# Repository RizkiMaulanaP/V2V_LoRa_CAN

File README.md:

# V2V LoRa CAN — Vehicle-to-Vehicle Collision Warning System

A research prototype for **vehicle-to-vehicle (V2V) safety messaging over LoRa**.
Each vehicle fuses GPS + IMU + OBD-II data, broadcasts its state to nearby
vehicles over a long-range LoRa link, and warns the driver (visual dashboard +
audible buzzer) of collision threats computed from the relative motion of
neighbours.

```
 ┌───────────── Vehicle A ─────────────┐         ┌──── Vehicle B ────┐
 │  GPS ┐                                │         │                   │
 │  IMU ┼─► ESP32 MCU ──USB──► Pi host   │  LoRa   │   ESP32 MCU ...   │
 │  OBD ┘   (firmware)  CDC   (UKF +     │◄═══════►│                   │
 │            │                warnings) │ 921 MHz │                   │
 │         GP4 buzzer ◄──CMD_BUZZER──┘   │         └───────────────────┘
 │            │                  │ TCP JSON :8765
 │         3 status LEDs         ▼
 └────────────────────────  Flutter dashboard (phone / desktop)
```

- **Firmware** (ESP32 / SX1262) — sensor acquisition, LoRa TX/RX, buzzer + LEDs.
- **Host** (Python on a Raspberry Pi / laptop) — UKF sensor fusion, neighbour
  tracking, the collision-warning engine, and the JSON bridge to the app.
- **App** (Flutter) — the driver dashboard (gauges + differentiated warnings).
- **Simulator** — replays recorded drives into the app, no hardware needed.

See [`MEMORY.md`](MEMORY.md) for a condensed design reference.

---

## 1. Hardware (per vehicle)

| Block | Part | Interface |
|-------|------|-----------|
| MCU + radio | Heltec ESP32 + **SX1262** LoRa (Wireless-Tracker class) | — |
| GNSS | on-board GNSS (UC6580-class) | UART `Serial1` 115200, RX=GP33 TX=GP34, power enable GP3 |
| IMU | **BMI160** (accel ±8 g, gyro ±500 °/s) | SPI, CS=GP7 |
| CAN / OBD-II | **MCP2515** (8 MHz xtal) @ 500 kbit/s | SPI, CS=GP15, INT=GP16 |
| Display | ST7735 TFT (on-board) | — |
| Annunciator | active buzzer | GP4 |
| Status LEDs | CAN / LoRa / GPS activity | GP17 / GP6 / GP5 |
| Host link | USB CDC serial @ 921600 | — |

**Shared SPI bus** (MCP2515 + BMI160): SCK=GP9, MISO=GP11, MOSI=GP10.
PCB design files in [`pcb-design/`](pcb-design/).

---

## 2. LoRa radio

| Parameter | Value |
|-----------|-------|
| Frequency | 921 MHz (AS923) |
| TX power | 20 dBm |
| Bandwidth | 125 kHz |
| Spreading factor | **SF9** |
| Coding rate | 4/8 |
| Modem | LoRa, explicit header, CRC on |
| Airtime | ≈ 250 ms / frame (11-byte payload) |

### Transmit triggering — ETSI CAM-style
Instead of a fixed interval, a node broadcasts when its state has *changed
meaningfully*, so fast/turning vehicles update more often and parked ones go
quiet. Evaluated every 100 ms; transmit when **any** of:

- position moved **> 4 m**, or
- heading changed **> 4°**, or
- speed changed **≥ 2 km/h**,

bounded to **[500 ms, 2 s]** (the upper bound is a heartbeat). Hard-brake events
(EEBL) and host-driven alerts are sent immediately.

### Compact over-air payload — 11 bytes
To keep airtime low, the broadcast is a packed 11-byte message (vs a naïve
19-byte struct), little-endian per field:

| bytes | field | encoding | resolution |
|------|-------|----------|-----------|
| 0 | node_id (6b) \| alert (2b) | `(id<<2)\|alert` | 0..63 / 0..3 |
| 1 | heading | `v·360/256` | 1.41° |
| 2 | speed | km/h | 1 km/h |
| 3–5 | latitude | 24-bit, −90..+90 | ~1.2 m |
| 6–8 | longitude | 24-bit, −180..+180 | ~2.4 m |
| 9–10 | tx_ts | `millis() & 0xFFFF` | 1 ms (wraps 65 s) |

`alert`: `0` normal, `1` traffic-jam, `2` hard-brake. Codec + rationale in
[`examples/CompactPayload/`](examples/CompactPayload/).

---

## 3. Firmware (`V2V_LoRa_CAN.ino`)

`FW_VERSION 3`. Single-file Arduino sketch (Heltec ESP32 core).
> The `V2V_LoRa_TWAI/` folder is an alternate build using the ESP32 built-in
> TWAI controller instead of the MCP2515 — **not maintained / not in use**.

Responsibilities:
- **Sensor acquisition**: BMI160 @ 100 Hz, GNSS (TinyGPS++), OBD-II PID polling
  (speed / RPM / coolant) over CAN.
- **Host serial protocol** (USB CDC): length-typed frames
  `[0xAA | type | ts | payload | XOR-cksum | 0x55]`:

  | frame | id | bytes | contents |
  |-------|----|-------|----------|
  | IMU | 0x01 | 32 | ax/ay/az, gx/gy/gz |
  | GPS | 0x02 | 34 | lat/lon, speed, hdop, sats, fix |
  | OBD | 0x03 | 9 | speed |
  | OBD_EXT | 0x06 | 12 | RPM, coolant |
  | HELLO | 0x05 | 10 | node_id, fw_version |
  | LORA_RX | 0x04 | 30 | decoded neighbour + RSSI/SNR |

  Host→MCU commands `[0xBB | cmd | … | cksum | 0x55]`: `CMD_HELLO`,
  `CMD_UPDATE_STATE` (push fused pose back so broadcasts carry filtered data),
  `CMD_BROADCAST` (immediate alert), `CMD_BUZZER` (drive GP4; pattern in the
  alert byte).
- **LoRa**: pack/broadcast own state (compact), unpack neighbours in `OnRxDone`
  and forward to the host via `LORA_RX`.
- **EEBL**: `detectHardBrake()` flags own rapid deceleration (OBD speed drop) and
  broadcasts `ALERT_BRAKE` for ~2 s.
- **Buzzer** (GP4, full-volume, non-blocking pattern player): `1` warning = two
  quick beeps, `2` danger = that burst repeated ~2.5 s, `3` GPS = double-chirp.
- **Activity LEDs**: single non-blocking blink per CAN/LoRa/GPS event.

A standalone PWM buzzer-volume bench sketch lives in
[`examples/BuzzerPWM/`](examples/BuzzerPWM/) (production uses full volume).

---

## 4. Host (`python-app/`)

| File | Role |
|------|------|
| `main_ukf.py` | live host: reads MCU serial, runs fusion, streams JSON, drives buzzer |
| `v2v_fusion.py` | ego **UKF** (E,N,v,ψ) + per-neighbour **CTRV** Kalman tracks |
| `v2v_warnings.py` | shared collision-warning engine |
| `v2v_json.py` | JSON contract + threaded TCP broadcast server |
| `simulate_v2v.py` | CSV-replay host (no hardware) |
| `plot_path.py` | offline trajectory plot (ego + neighbours) |

### Warning engine
`assess(ego, neighbors, gps) → (warning, buzzer)`:

- **Closing speed & TTC** from relative velocity.
- **Speed-scaled thresholds** (TTC bands + headway distance, not fixed radii).
- **Path / approach filtering** (only converging, in-corridor neighbours warn;
  classifies forward / cross / rear).
- **EEBL** for a same-heading lead vehicle broadcasting a brake flag.
- **GPS-lost / low-accuracy** ego warning.
- Per-node buzzer cooldown (warning re-beeps ≤ once / 5 s; danger re-arms ~2.5 s).

### JSON contract (host → app, newline-delimited, TCP :8765)
```json
{
  "ts": 123456,
  "ego": {"lat","lon","x","y","speed_kmh","heading_deg",
          "engine_rpm","engine_temp_c","fuel_level_pct",
          "fix_valid","hdop","satellites"},
  "neighbors": [{"id","lat","lon","x","y","speed_kmh","heading_deg",
                 "emergency_status"}],
  "warning": {"level","type","direction","distance_m","ttc_s",
              "closing_kmh","neighbor_id"}   // or null
}
```
Full spec: [`Flutter-App/v2v/docs/DATA_CONTRACT.md`](Flutter-App/v2v/docs/DATA_CONTRACT.md).

---

## 5. App (`Flutter-App/v2v/`)

Driver dashboard: RPM + speed gauges, engine temp/fuel, and a central
**warning card**. Data sources are swappable in `home_screen.dart`:
`TcpDataSource` (live host / simulator), `MockDataSource` (offline CSV),
`SerialDataSource`, `JsonlFileDataSource`.

Warnings are **host-computed** and merely rendered, with differentiated types:
forward-collision, emergency-brake, cross-traffic, approaching-rear,
emergency-broadcast, GPS-lost — each with its own icon/colour, plus distance /
TTC / closing speed and a GPS-health chip.

---

## 6. Build & run

### Firmware
Arduino IDE / arduino-cli with the **Heltec ESP32** board package. Set a unique
`NODE_ID` per vehicle, flash both nodes (SF and air format must match → same
firmware version on every node), open serial @ 921600.

### Host
```bash
cd python-app
pip install pyserial numpy scipy matplotlib filterpy pandas
python main_ukf.py --json-tcp 8765           # auto-detect MCU; serve app on :8765
# pin the serial port if needed:
python main_ukf.py --port /dev/ttyACM0 --json-tcp 8765
```

### App
```bash
cd Flutter-App/v2v
flutter pub get
flutter run -d linux        # dashboard connects to localhost:8765
```
For a phone/tablet, set `TcpDataSource(host: '<PC-LAN-IP>')` in
`lib/presentation/screens/home_screen.dart` (server binds `0.0.0.0`).

### Simulator (no hardware)
```bash
cd python-app
python simulate_v2v.py --loop                # replay newest recording → :8765
python simulate_v2v.py --inject-brake 60     # demo an EEBL event at t=60 s
python simulate_v2v.py --serial /dev/ttyACM0 # also drive a bench buzzer
```

---

## 7. Repository layout
```
V2V_LoRa_CAN.ino        firmware (MCP2515 CAN variant — in use)
V2V_LoRa_TWAI/          firmware (ESP32 TWAI variant — unused)
python-app/             host, fusion, warning engine, simulator, tools
Flutter-App/v2v/        driver dashboard
examples/CompactPayload/ over-air payload codec + spec
examples/BuzzerPWM/     buzzer PWM volume bench sketch
pcb-design/             hardware design files
BMI160-Arduino/         IMU library
MEMORY.md               condensed design reference
```

---

## 8. Status & limitations
- Two-node tested; firmware is single-file and board-specific (Heltec).
- No listen-before-talk (CAD was evaluated and removed) — short CAM intervals
  raise collision exposure slightly.
- LoRa duty cycle exceeds the 1 % AS923 regulatory limit at short intervals;
  this is a **research prototype**, tune `CAM_T_MIN_MS` / SF for compliant use.
- `tx_ts` wraps every ~65 s (one-way latency only).
- Research/educational project — not a certified safety system.

## License
See [`LICENSE`](LICENSE).

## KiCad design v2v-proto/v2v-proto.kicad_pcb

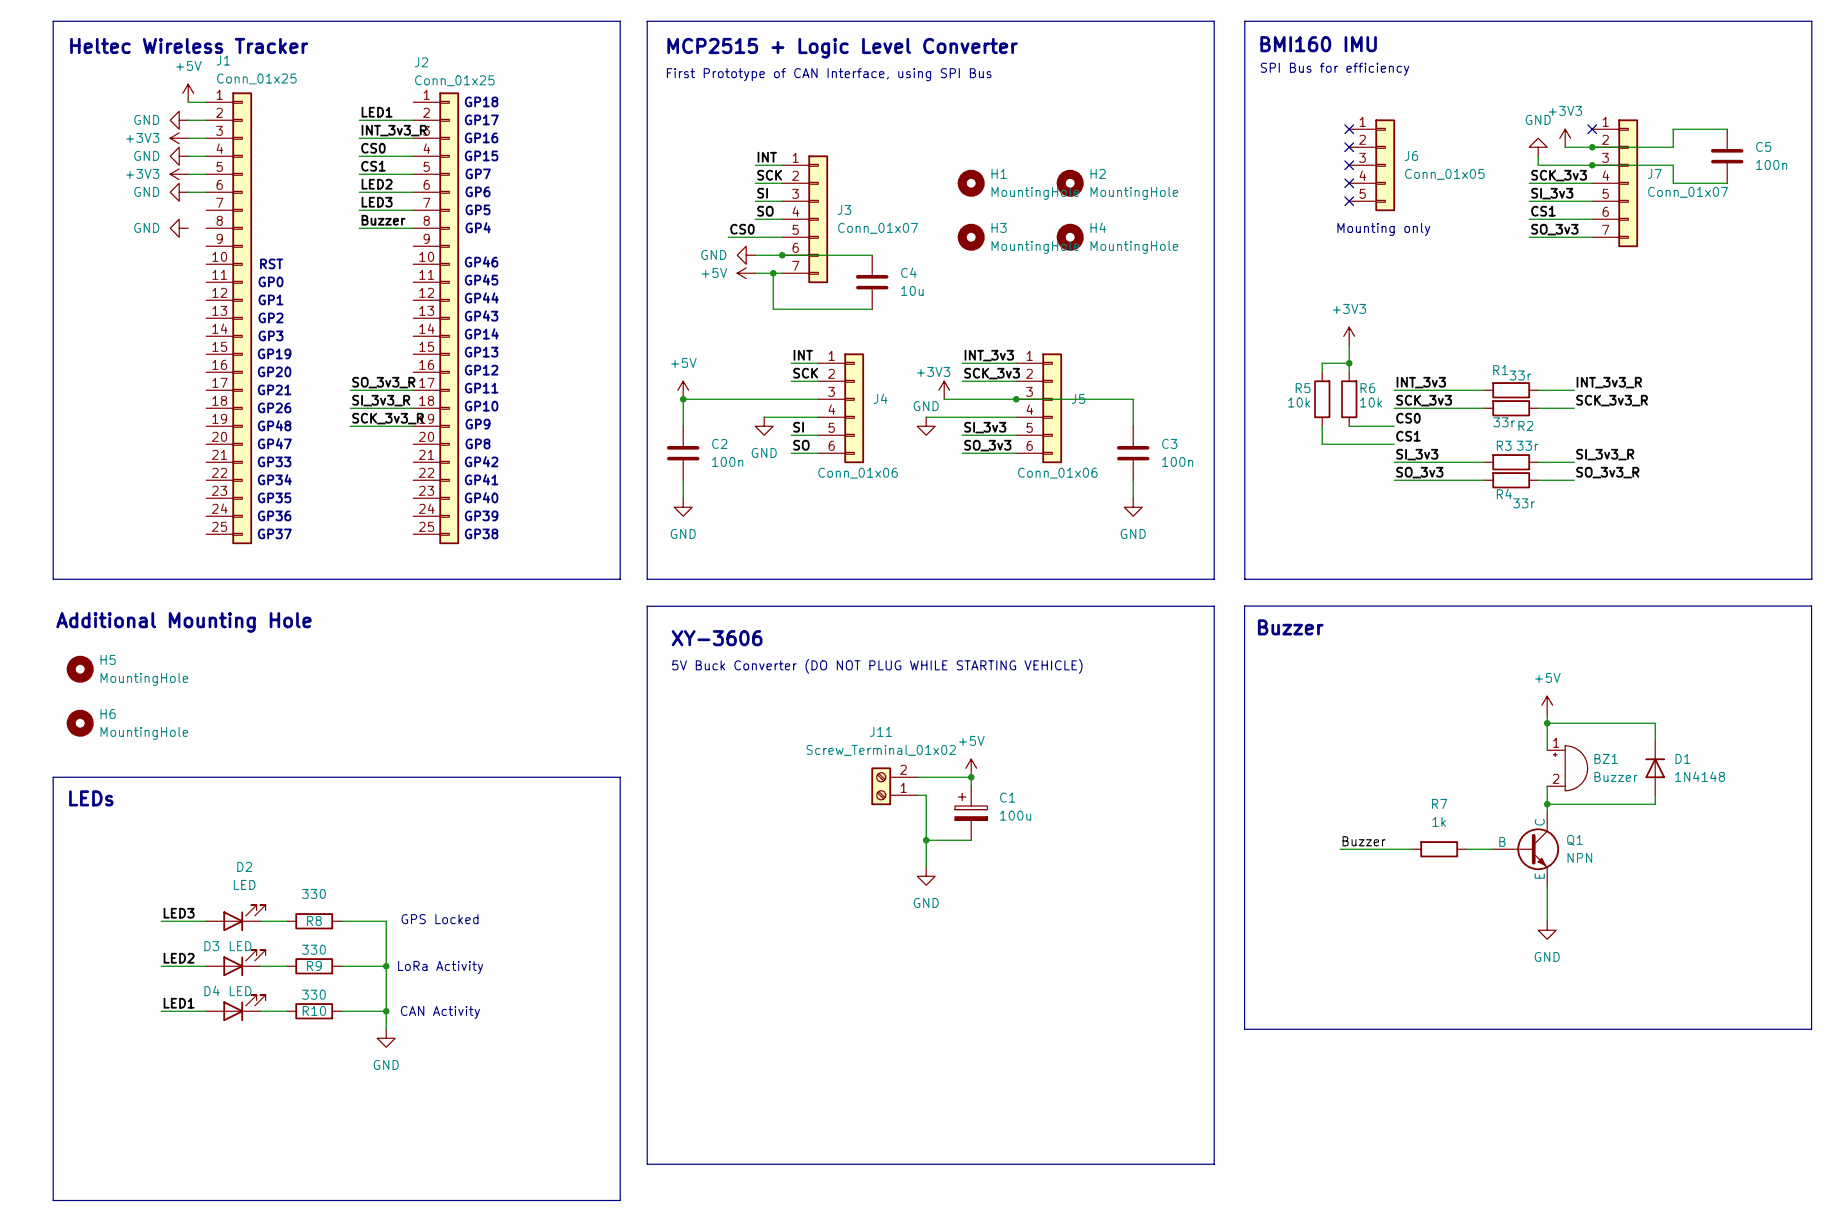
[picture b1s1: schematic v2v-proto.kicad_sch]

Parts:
BZ1: Buzzer; Buzzer_12x9.5RM7.6
C1: 100u; CP_Elec_6.3x5.3
C2, C3, C5: 100n; C_0805_2012Metric_Pad1.18x1.45mm_HandSolder
C4: 10u; C_1206_3216Metric_Pad1.33x1.80mm_HandSolder
D1: 1N4148; D_DO-35_SOD27_P7.62mm_Horizontal
D2, D3, D4: LED; LED_0805_2012Metric
H1, H2, H3, H4, H5, H6: MountingHole; MountingHole_3.2mm_M3
J1, J2: Conn_01x25; PinHeader_1x25_P2.54mm_Vertical
J3, J7: Conn_01x07; PinHeader_1x07_P2.54mm_Vertical
J4, J5: Conn_01x06; PinHeader_1x06_P2.54mm_Vertical
J6: Conn_01x05; PinHeader_1x05_P2.54mm_Vertical
J11: Screw_Terminal_01x02; TerminalBlock_MaiXu_MX126-5.0-02P_1x02_P5.00mm
Q1: NPN; TO-92
R1, R2, R3, R4: 33r; R_1206_3216Metric_Pad1.30x1.75mm_HandSolder
R5, R6: 10k; R_0805_2012Metric_Pad1.20x1.40mm_HandSolder
R7: 1k; R_0805_2012Metric_Pad1.20x1.40mm_HandSolder
R8, R9, R10: 330; R_0805_2012Metric_Pad1.20x1.40mm_HandSolder

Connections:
+3V3: C3.1, C5.1, J1.3, J1.5, J5.3, J7.2, R5.2, R6.2
+5V: BZ1.1 (+), C1.1, C2.1, C4.1, D1.1 (K), J1.1, J3.7, J4.3, J11.2
/Buzzer: J2.8, R7.2
/CS0: J2.4, J3.5, R6.1
/CS1: J2.5, J7.6, R5.1
/INT: J3.1, J4.1
/INT_3v3: J5.1, R1.2
/INT_3v3_R: J2.3, R1.1
/LED1: D4.2 (A), J2.2
/LED2: D3.2 (A), J2.6
/LED3: D2.2 (A), J2.7
/SCK: J3.2, J4.2
/SCK_3v3: J5.2, J7.4, R2.2
/SCK_3v3_R: J2.19, R2.1
/SI: J3.3, J4.5
/SI_3v3: J5.5, J7.5, R3.2
/SI_3v3_R: J2.18, R3.1
/SO: J3.4, J4.6
/SO_3v3: J5.6, J7.7, R4.2
/SO_3v3_R: J2.17, R4.1
GND: C1.2, C2.2, C3.2, C4.2, C5.2, J1.2, J1.4, J1.6, J3.6, J4.4, J5.4, J7.3, J11.1, Q1.3 (E), R8.2, R9.2, R10.2
unnamed: BZ1.2 (-), D1.2 (A), Q1.1 (C)
unnamed: D2.1 (K), R8.1
unnamed: D3.1 (K), R9.1
unnamed: D4.1 (K), R10.1
unnamed: Q1.2 (B), R7.1

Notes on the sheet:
GP6
GP21
GP18
Additional Mounting Hole
CAN Activity
GP1
First Prototype of CAN Interface, using SPI Bus
GP48
GP7
GP39
GP26
GP44
GP14
GP17
GPS Locked
GP46
GP2
GP40
GP43
RST
GP38
XY-3606
GP20
GP35
Buzzer
GP37
GP3
GP41
LEDs
GP19
GP33
GP11
GP42
GP12
SPI Bus for efficiency
GP16
GP9
GP13
GP0
5V Buck Converter (DO NOT PLUG WHILE STARTING VEHICLE)

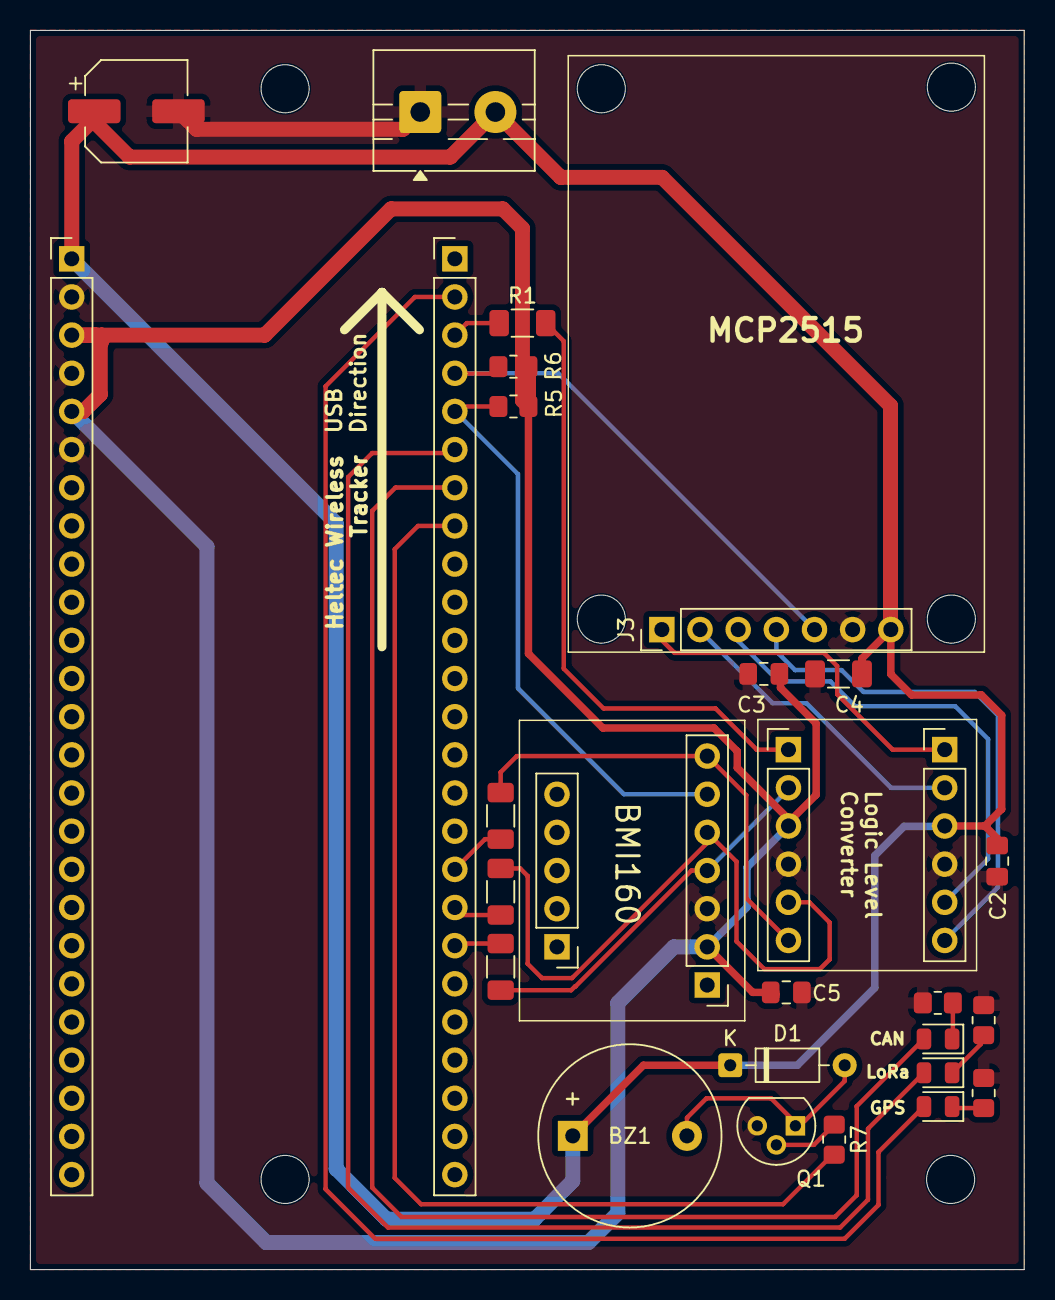
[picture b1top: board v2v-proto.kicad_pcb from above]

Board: 2 copper layers, 66.2 x 82.5 mm, 36 parts (0 on the bottom side), 26 nets.

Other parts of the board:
H6#2: MountingHole; MountingHole_3.2mm_M3

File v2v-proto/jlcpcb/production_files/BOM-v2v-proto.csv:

Comment,Designator,Footprint,LCSC,Quantity
Conn_01x07,J7,PinHeader_1x07_P2.54mm_Vertical,,1
10u,C4,C_1206_3216Metric_Pad1.33x1.80mm_HandSolder,,1
100n,C5,C_0805_2012Metric_Pad1.18x1.45mm_HandSolder,,1
10k,R5,R_0805_2012Metric_Pad1.20x1.40mm_HandSolder,,1
330,R9,R_0805_2012Metric_Pad1.20x1.40mm_HandSolder,,1
100n,C3,C_0805_2012Metric_Pad1.18x1.45mm_HandSolder,,1
LED,D4,LED_0805_2012Metric,,1
33r,R1,R_1206_3216Metric_Pad1.30x1.75mm_HandSolder,,1
Conn_01x05,J6,PinHeader_1x05_P2.54mm_Vertical,,1
1k,R7,R_0805_2012Metric_Pad1.20x1.40mm_HandSolder,,1
33r,R4,R_1206_3216Metric_Pad1.30x1.75mm_HandSolder,,1
NPN,Q1,TO-92,,1
Conn_01x06,J4,PinHeader_1x06_P2.54mm_Vertical,,1
Conn_01x25,J2,PinHeader_1x25_P2.54mm_Vertical,,1
10k,R6,R_0805_2012Metric_Pad1.20x1.40mm_HandSolder,,1
100n,C2,C_0805_2012Metric_Pad1.18x1.45mm_HandSolder,,1
33r,R3,R_1206_3216Metric_Pad1.30x1.75mm_HandSolder,,1
33r,R2,R_1206_3216Metric_Pad1.30x1.75mm_HandSolder,,1
Conn_01x07,J3,PinHeader_1x07_P2.54mm_Vertical,,1
Screw_Terminal_01x02,J11,TerminalBlock_MaiXu_MX126-5.0-02P_1x02_P5.00mm,,1
100u,C1,CP_Elec_6.3x5.3,,1
Conn_01x25,J1,PinHeader_1x25_P2.54mm_Vertical,,1
Buzzer,BZ1,Buzzer_12x9.5RM7.6,,1
330,R10,R_0805_2012Metric_Pad1.20x1.40mm_HandSolder,,1
Conn_01x06,J5,PinHeader_1x06_P2.54mm_Vertical,,1
LED,D3,LED_0805_2012Metric,,1
LED,D2,LED_0805_2012Metric,,1
1N4148,D1,D_DO-35_SOD27_P7.62mm_Horizontal,,1
330,R8,R_0805_2012Metric_Pad1.20x1.40mm_HandSolder,,1

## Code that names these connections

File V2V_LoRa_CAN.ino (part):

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// STATUS DISPLAY + BUZZER (proto board)
// Built-in ST7735 TFT shares Vext/VGNSS_CTRL (GPIO3).
// ==========================================
#define BUZZER_PIN   4      // active buzzer — single beep on config error

// Activity LEDs — blink once per detected event (non-blocking).
#define LED_CAN_PIN   17    // LED1: CAN frame received
#define LED_LORA_PIN  6     // LED2: LoRa packet TX/RX
#define LED_GPS_PIN   5     // LED3: GPS sentence decoded
#define LED_BLINK_MS  30    // on-time per blink

// ==========================================
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#define CMD_BROADCAST       0x01   // Immediate LoRa alert TX with provided data
#define CMD_UPDATE_STATE    0x02   // Update state used in next periodic TX
#define CMD_HELLO           0x03   // Host handshake / heartbeat
#define CMD_BUZZER          0x04   // Drive GP4 buzzer; pattern id in alert_type

// V2V alert_type encoding (broadcast in V2V_Payload, shared with host/app).
#define ALERT_NORMAL        0
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        case BUZZ_GPS:     buzzSteps = BUZZ_PAT_GPS;
                           buzzLen = sizeof(BUZZ_PAT_GPS)/sizeof(uint16_t);     break;
        default:           buzzSteps = nullptr; buzzLen = 0;
                           digitalWrite(BUZZER_PIN, LOW); return;
    }
    digitalWrite(BUZZER_PIN, HIGH);          // step 0 is always ON
    buzzStepUntil = millis() + buzzSteps[0];
}

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    if (millis() < buzzStepUntil) return;
    buzzStep++;
    if (buzzStep >= buzzLen) {                // pattern finished
        digitalWrite(BUZZER_PIN, LOW);
        buzzSteps = nullptr;
        buzzPattern = BUZZ_OFF;
        return;
    }
    digitalWrite(BUZZER_PIN, (buzzStep & 1) ? LOW : HIGH);  // even=ON, odd=OFF
    buzzStepUntil = millis() + buzzSteps[buzzStep];
}

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    my_data.alert_type  = 0;

    // --- Buzzer ---
    pinMode(BUZZER_PIN, OUTPUT);
    digitalWrite(BUZZER_PIN, LOW);

    // --- Activity LEDs ---
    pinMode(LED_CAN_PIN,  OUTPUT);
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
    if (err || warn) {
        // Single notification beep
        digitalWrite(BUZZER_PIN, HIGH);
        delay(300);
        digitalWrite(BUZZER_PIN, LOW);
    }
}

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
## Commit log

2026-06-15 Convert nested repositories to regular folders and track files
2026-06-15 Updated main_ukf.py
